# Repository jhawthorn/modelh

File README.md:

# Model H
Replacement Model M controller board

Still a work in progress.

## Part list

* CONN FFC VERT 16POS 2.54MM PCB - https://www.digikey.ca/products/en?keywords=A144434-ND
* CONN FFC VERT 8POS 2.54MM PCB - https://www.digikey.ca/products/en?keywords=5-520315-8-ND
* CONN FFC VERT 4POS 2.54MM PCB - https://www.digikey.ca/products/en?keywords=A123169-ND

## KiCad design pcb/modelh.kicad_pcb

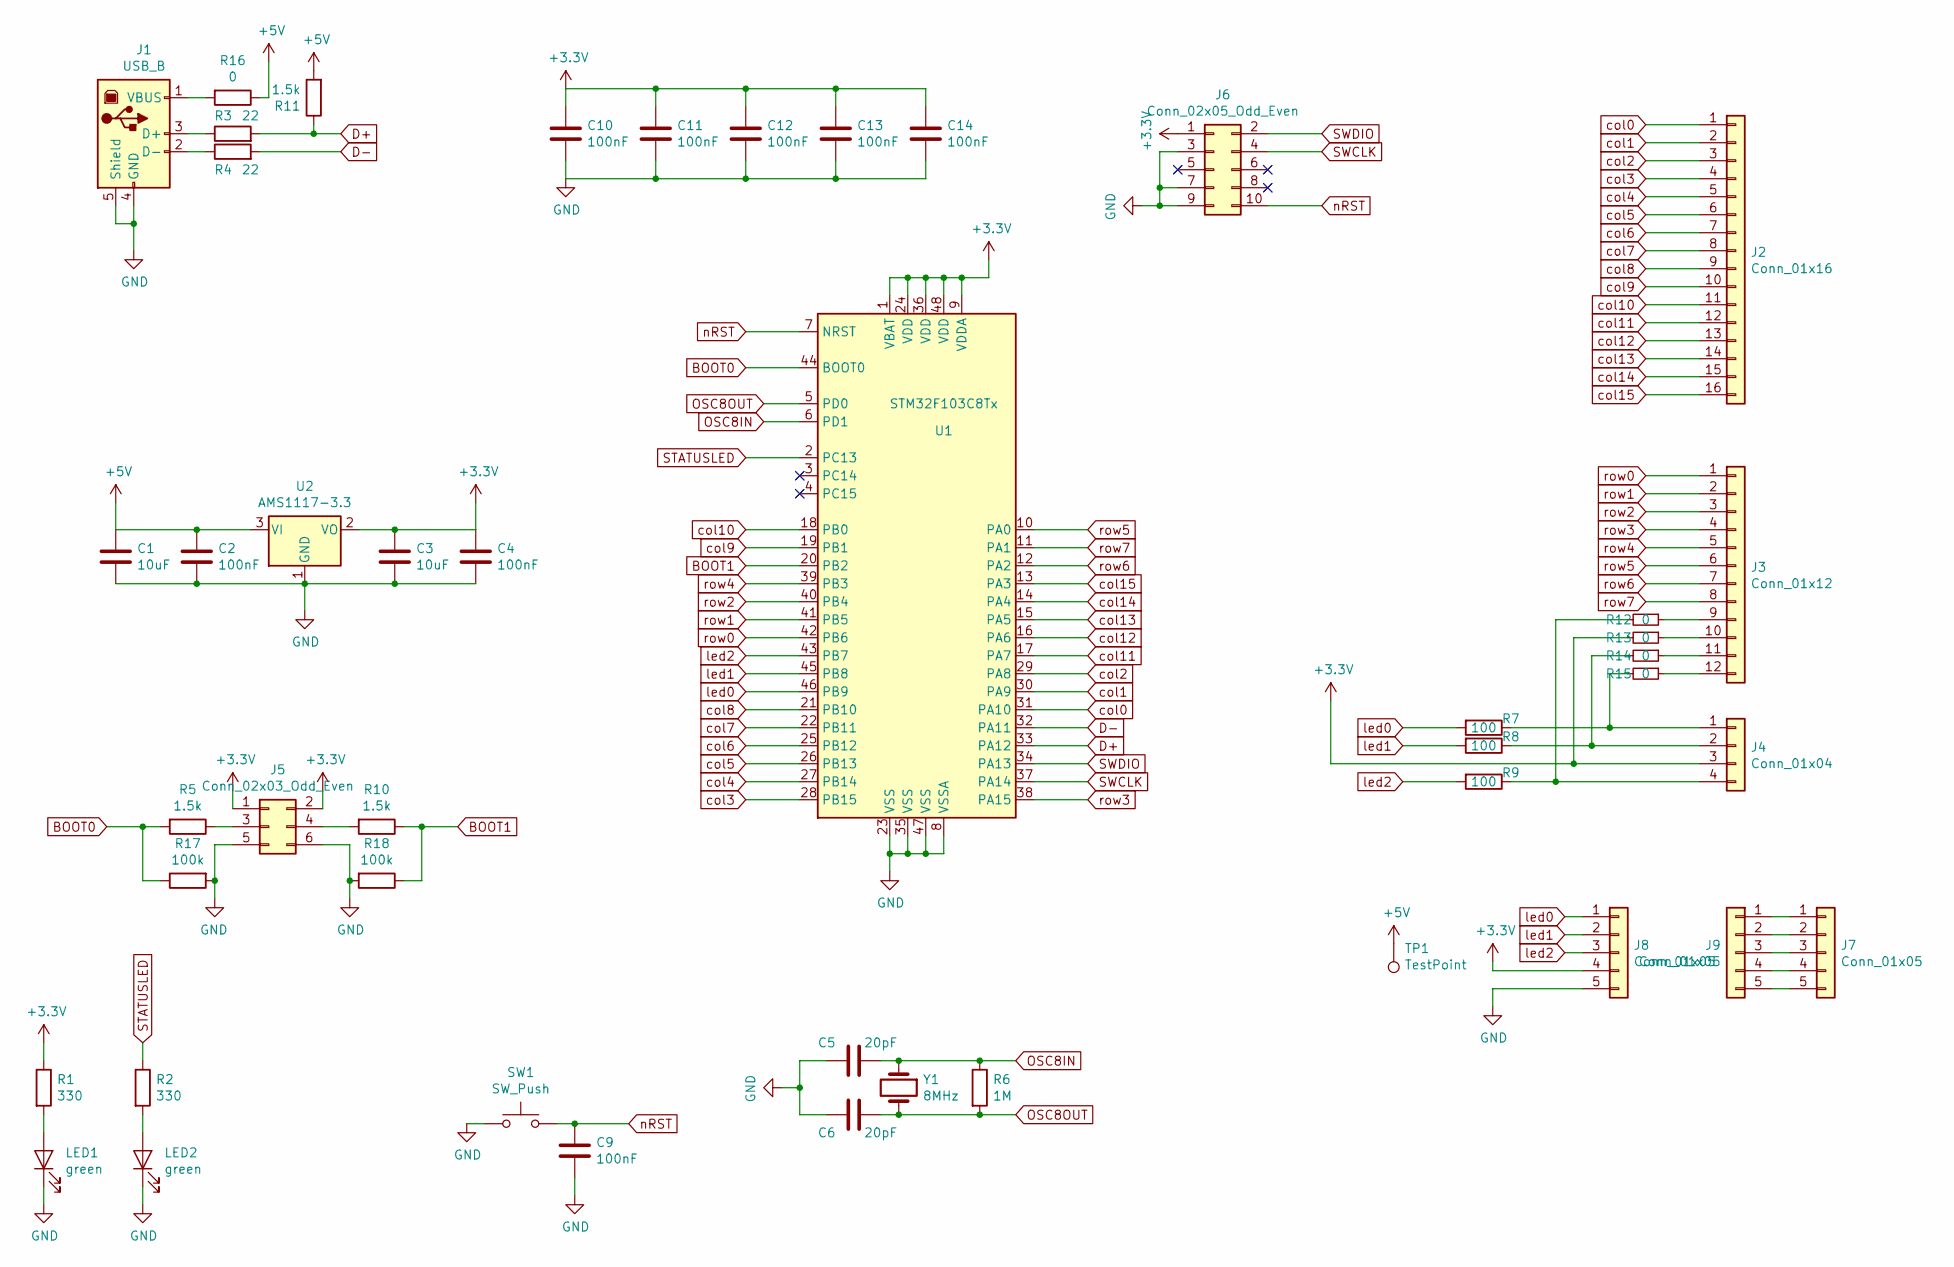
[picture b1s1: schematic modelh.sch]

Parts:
C1, C3: 10uF; C_0603_1608Metric; LCSC C19702
C2, C4, C9, C10, C11, C12, C13, C14: 100nF; C_0402_1005Metric; LCSC C1525
C5, C6: 20pF; C_0603_1608Metric; LCSC C1653
J1: USB_B; USB_B_OST_USB-B1HSxx_Horizontal
J2: Conn_01x16; PinSocket_1x16_P2.54mm_Vertical
J3: Conn_01x12; PinSocket_1x12_P2.54mm_Vertical
J4: Conn_01x04; PinSocket_1x04_P2.54mm_Vertical
J5: Conn_02x03_Odd_Even; PinHeader_2x03_P2.54mm_Vertical
J6: Conn_02x05_Odd_Even; IDC-Header_2x05_P2.54mm_Vertical
J7, J8, J9: Conn_01x05; PinSocket_1x05_P2.54mm_Vertical
LED1, LED2: green; LED_0805_2012Metric; LCSC C2297
R1, R2: 330; R_0603_1608Metric; LCSC C23138
R3, R4: 22; R_0603_1608Metric; LCSC C23345
R5, R10, R11: 1.5k; R_0603_1608Metric; LCSC C22843
R6: 1M; R_0603_1608Metric; LCSC C22935
R7, R8, R9: 100; R_0805_2012Metric; LCSC C17408
R12, R13, R14, R15, R16: 0; R_0805_2012Metric_Pad1.15x1.40mm_HandSolder; LCSC C17477
R17, R18: 100k; R_0603_1608Metric; LCSC C25803
SW1: SW_Push; SW_SPST_EVPBF; LCSC C318888
TP1: TestPoint; TestPoint_THTPad_D1.5mm_Drill0.7mm
U1: STM32F103C8Tx; LQFP-48_7x7mm_P0.5mm; LCSC C8734
U2: AMS1117-3.3; SOT-223-3_TabPin2; LCSC C6186
Y1: 8MHz; Crystal_SMD_5032-2Pin_5.0x3.2mm; LCSC C115962

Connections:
+3V3: C3.1, C4.1, C10.1, C11.1, C12.1, C13.1, C14.1, J4.3, J5.1, J5.2, J6.1, J8.4, R1.1, R13.2, U1.1 (VBAT), U1.9 (VDDA), U1.24 (VDD), U1.36 (VDD), U1.48 (VDD), U2.2 (VO)
+5V: C1.1, C2.1, R11.2, R16.1, TP1.1, U2.3 (VI)
BOOT0: R5.2, R17.1, U1.44 (BOOT0)
BOOT1: R10.1, R18.1, U1.20 (PB2)
D+: R3.2, R11.1, U1.33 (PA12)
D-: R4.2, U1.32 (PA11)
GND: C1.2, C2.2, C3.2, C4.2, C5.2, C6.2, C9.2, C10.2, C11.2, C12.2, C13.2, C14.2, J1.4 (GND), J1.5 (Shield), J5.5, J5.6, J6.3, J6.7, J6.9, J8.5, LED1.1 (K), LED2.1 (K), R17.2, R18.2, SW1.1, U1.8 (VSSA), U1.23 (VSS), U1.35 (VSS), U1.47 (VSS), U2.1 (GND)
unnamed: J1.1 (VBUS), R16.2
unnamed: J1.2 (D-), R4.1
unnamed: J1.3 (D+), R3.1
unnamed: J3.9, R12.1
unnamed: J3.10, R13.1
unnamed: J3.11, R14.1
unnamed: J3.12, R15.1
unnamed: J4.1, R7.1, R15.2
unnamed: J4.2, R8.1, R14.2
unnamed: J4.4, R9.1, R12.2
unnamed: J5.3, R5.1
unnamed: J5.4, R10.2
unnamed: J7.1, J9.1
unnamed: J7.2, J9.2
unnamed: J7.3, J9.3
unnamed: J7.4, J9.4
unnamed: J7.5, J9.5
unnamed: LED1.2 (A), R1.2
unnamed: LED2.2 (A), R2.2
OSC8IN: C5.1, R6.1, U1.6 (PD1), Y1.1
OSC8OUT: C6.1, R6.2, U1.5 (PD0), Y1.2
STATUSLED: R2.1, U1.2 (PC13)
SWCLK: J6.4, U1.37 (PA14)
SWDIO: J6.2, U1.34 (PA13)
col0: J2.1, U1.31 (PA10)
col1: J2.2, U1.30 (PA9)
col2: J2.3, U1.29 (PA8)
col3: J2.4, U1.28 (PB15)
col4: J2.5, U1.27 (PB14)
col5: J2.6, U1.26 (PB13)
col6: J2.7, U1.25 (PB12)
col7: J2.8, U1.22 (PB11)
col8: J2.9, U1.21 (PB10)
col9: J2.10, U1.19 (PB1)
col10: J2.11, U1.18 (PB0)
col11: J2.12, U1.17 (PA7)
col12: J2.13, U1.16 (PA6)
col13: J2.14, U1.15 (PA5)
col14: J2.15, U1.14 (PA4)
col15: J2.16, U1.13 (PA3)
led0: J8.1, R7.2, U1.46 (PB9)
led1: J8.2, R8.2, U1.45 (PB8)
led2: J8.3, R9.2, U1.43 (PB7)
nRST: C9.1, J6.10, SW1.2, U1.7 (NRST)
row0: J3.1, U1.42 (PB6)
row1: J3.2, U1.41 (PB5)
row2: J3.3, U1.40 (PB4)
row3: J3.4, U1.38 (PA15)
row4: J3.5, U1.39 (PB3)
row5: J3.6, U1.10 (PA0)
row6: J3.7, U1.12 (PA2)
row7: J3.8, U1.11 (PA1)

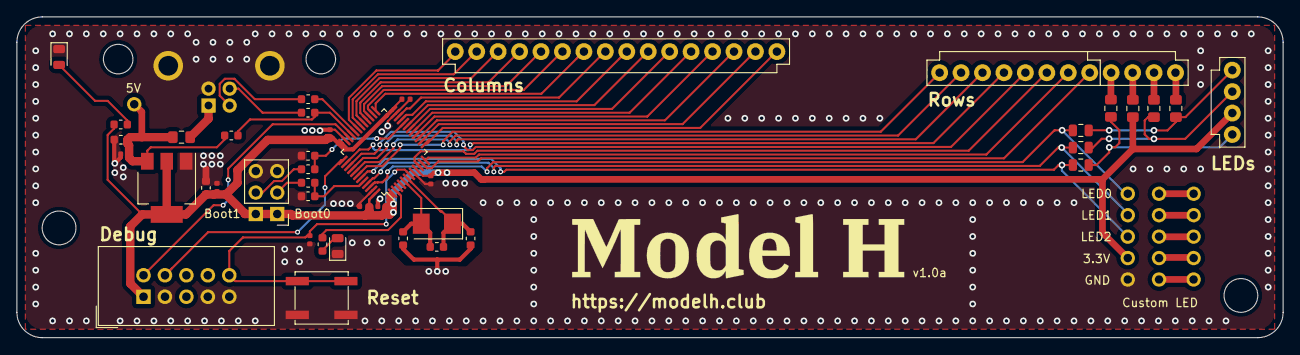
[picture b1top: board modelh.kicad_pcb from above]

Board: 2 copper layers, 150.0 x 38.0 mm, 46 parts (0 on the bottom side), 59 nets.

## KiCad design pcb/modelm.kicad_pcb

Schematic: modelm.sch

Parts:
C1, C2: 0.1uF; C_Disc_D4.7mm_W2.5mm_P5.00mm
J2: Conn_01x16; PinHeader_1x16_P2.54mm_Vertical
J3: Conn_01x08; PinHeader_1x08_P2.54mm_Vertical
J4: Conn_01x04; PinHeader_1x04_P2.54mm_Vertical
R4, R5, R6: 120; R_Axial_DIN0207_L6.3mm_D2.5mm_P10.16mm_Horizontal
U1: ProMicro
U2, U3: MCP23S17_SP; DIP-28_W7.62mm

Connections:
+5V: C1.2, C2.2, J4.3, U1.21, U2.9, U2.15, U2.18, U3.9, U3.18
/CS_io: U1.20, U2.11, U3.11
/MISO: U1.15, U2.14, U3.14
/MOSI: U1.14, U2.13, U3.13
/SCK: U1.16, U2.12, U3.12
/col0: J2.1, U3.28
/col1: J2.2, U3.27
/col2: J2.3, U3.26
/col3: J2.4, U3.25
/col4: J2.5, U3.24
/col5: J2.6, U3.23
/col6: J2.7, U3.22
/col7: J2.8, U3.21
/col8: J2.9, U3.1
/col9: J2.10, U3.2
/col10: J2.11, U3.3
/col11: J2.12, U3.4
/col12: J2.13, U3.5
/col13: J2.14, U3.6
/col14: J2.15, U3.7
/col15: J2.16, U3.8
/led0: R4.2, U2.1
/led1: R5.2, U2.2
/led2: R6.2, U2.3
/row0: J3.1, U2.28
/row1: J3.2, U2.27
/row2: J3.3, U2.26
/row3: J3.4, U2.25
/row4: J3.5, U2.24
/row5: J3.6, U2.23
/row6: J3.7, U2.22
/row7: J3.8, U2.21
GND: C1.1, C2.1, U1.3, U1.4, U1.23, U2.10, U2.16, U2.17, U3.10, U3.15, U3.16, U3.17
unnamed: J4.1, R4.1
unnamed: J4.2, R5.1
unnamed: J4.4, R6.1

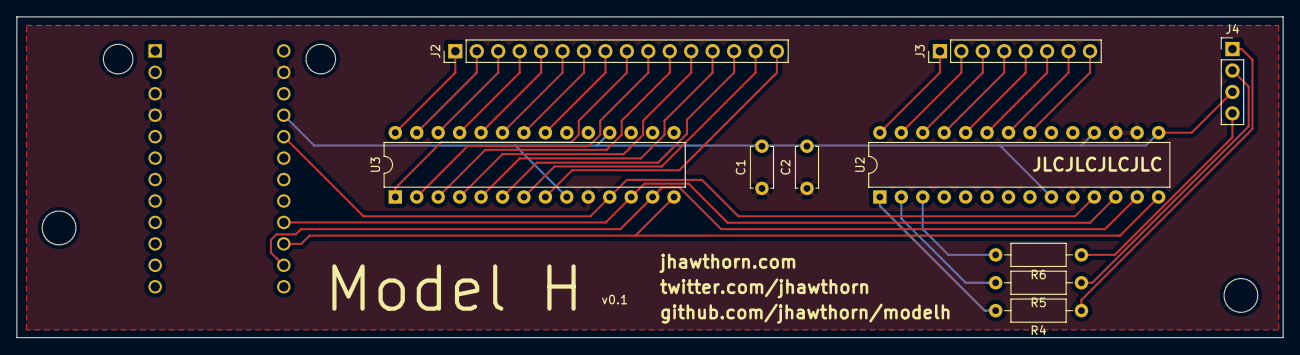
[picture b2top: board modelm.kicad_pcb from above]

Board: 2 copper layers, 150.0 x 38.0 mm, 11 parts (0 on the bottom side), 36 nets.

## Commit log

2020-05-14 Version 0.1 PCB
2020-05-14 Delete v1 pcb
    This reverts commit 9b523ded0fd16e196e9a7f727c18c3003cbd98c2.
2020-05-14 Start of model H design
2020-05-16 Add PCB template
2020-05-17 Maybe completed v0.2?
2020-05-17 Fix resistor sizes
2020-05-17 More work
2020-07-06 PCB updates
2020-07-06 Remove sch-bak
2020-07-11 Fix DRC
2020-07-12 Attempt at supporting 12 pin keyboards
2020-07-12 Remove LSE oscillator
2020-07-12 Make boot selection pins optional
2020-07-12 Create testpoints for custom LEDs
2020-07-14 WIPWIP
2020-07-14 Start on custom footprints
2020-07-14 Finish footprints
2020-07-14 Remove misnamed footprint
2020-07-14 cleanup testpoint footprints
2020-07-14 ground stitching
2020-07-14 nearly done
2020-07-25 Add shim model
2020-07-25 Fix text on silkscreen
2020-07-25 Adjust shim
2020-08-23 Adjust shim heights
2020-08-23 Round tabs on shim
2020-08-30 Add extra support ridge to shim
2020-09-21 Add a website
2020-09-21 Add hacky makefile to help making production files
2020-09-21 Specify height?
2020-09-25 Adds trapezoid shape to 3D printed shim
    Adds trapezoid shape to 3D printed shim to fit better in the keyboard case.
2020-09-26 site updates
2020-09-26 Fix typos
